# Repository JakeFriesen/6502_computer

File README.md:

2020-05-02
Jake Friesen
Using the VASM oldstyle assembler to convert assembly to a binary output for 6502 computers:

1) open CMD and cd to this folder, and have your assembly.txt in this folder
2) run the following command:
	vasm6502_oldstyle.exe -Fbin -dotdir YourFile.txt
-Fbin: outputs a binary file
-dotdir: uses the "." directives (like .org)
The binary file is the a.out file

3) open Xgpro, put the a.out file in, and configure for the right chip (ATMEL AT28C256)
4) load the chip into the programmer, and click "program"

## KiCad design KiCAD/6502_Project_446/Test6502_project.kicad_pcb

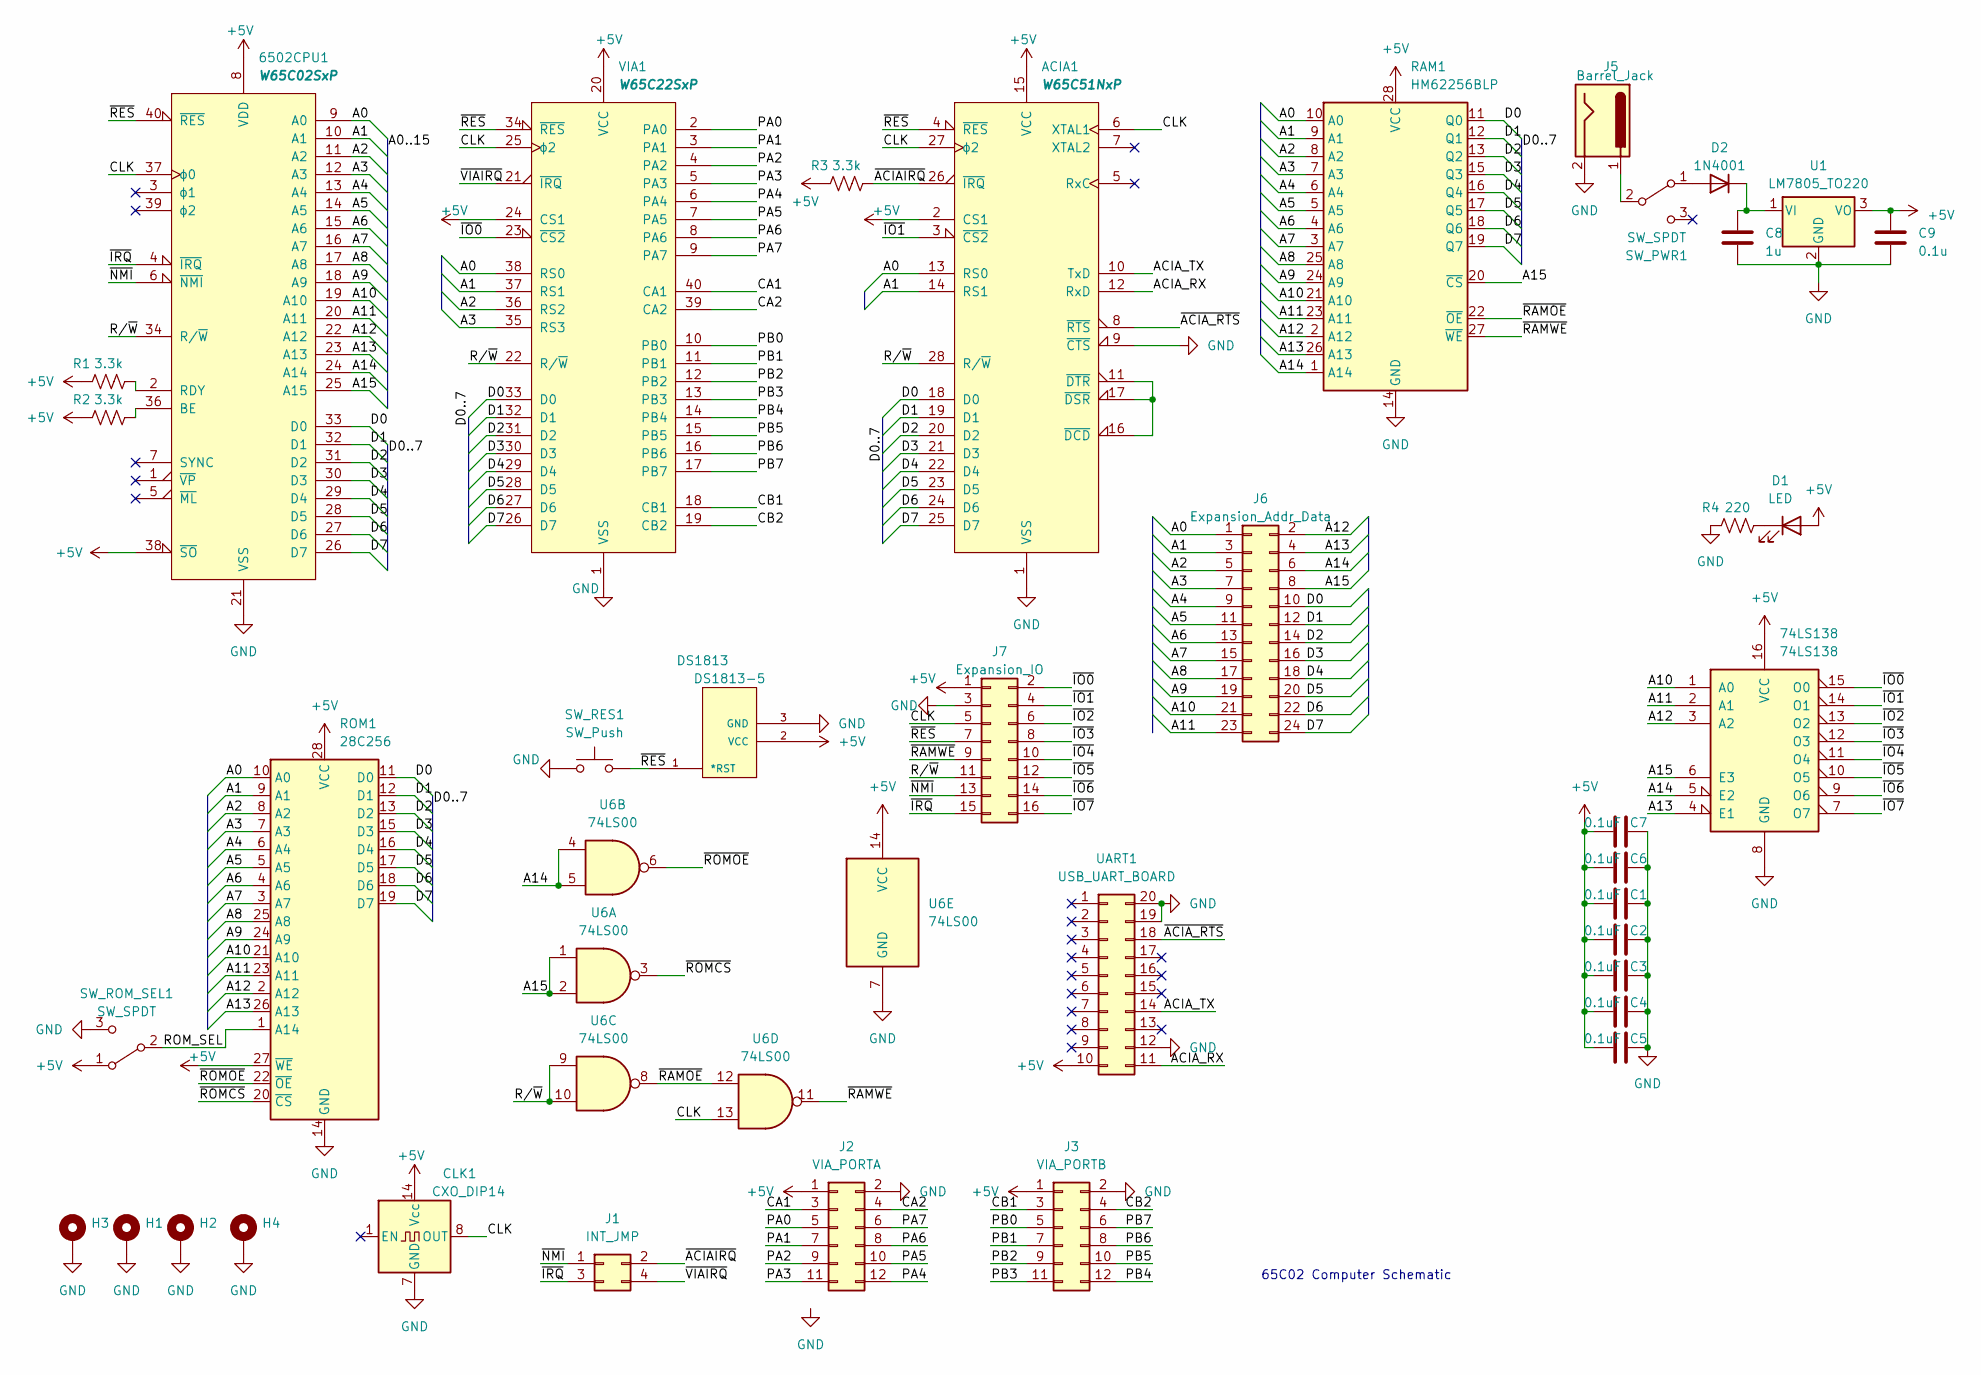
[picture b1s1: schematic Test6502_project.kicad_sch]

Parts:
74LS138: 74LS138; DIP-16_W7.62mm
6502CPU1: W65C02SxP; DIP-40_W15.24mm_Socket
ACIA1: W65C51NxP; DIP-28_W15.24mm_Socket
C1, C2, C3, C4, C5, C6, C7: 0.1uF; C_Disc_D5.0mm_W2.5mm_P2.50mm
C8: 1u; C_Disc_D5.0mm_W2.5mm_P2.50mm
C9: 0.1u; C_Disc_D5.0mm_W2.5mm_P2.50mm
CLK1: CXO_DIP14; Oscillator_DIP-14
D1: LED; LED_D3.0mm
D2: 1N4001; D_DO-41_SOD81_P10.16mm_Horizontal
DS1813: DS1813-5; 21-0248A; MANUFACTURER_PART_NUMBER ds18135+
H1, H2, H3, H4: MountingHole_Pad; MountingHole_3.2mm_M3_DIN965_Pad
J1: INT_JMP; PinHeader_2x02_P2.54mm_Vertical
J2: VIA_PORTA; PinHeader_2x06_P2.54mm_Vertical
J3: VIA_PORTB; PinHeader_2x06_P2.54mm_Vertical
J5: Barrel_Jack; BarrelJack_Horizontal
J6: Expansion_Addr_Data; PinHeader_2x12_P2.54mm_Vertical
J7: Expansion_IO; PinHeader_2x08_P2.54mm_Vertical
R1, R2, R3: 3.3k; R_Axial_DIN0207_L6.3mm_D2.5mm_P7.62mm_Horizontal
R4: 220; R_Axial_DIN0207_L6.3mm_D2.5mm_P7.62mm_Horizontal
RAM1: HM62256BLP; DIP-28_W15.24mm_Socket
ROM1: 28C256; DIP-28_W15.24mm_Socket
SW_PWR1: SW_SPDT; SW_THT_DPDT
SW_RES1: SW_Push; SW_PUSH_6mm
SW_ROM_SEL1: SW_SPDT; SW_THT_DPDT
U1: LM7805_TO220; TO-220-3_Vertical
U6: 74LS00; DIP-14_W7.62mm
UART1: USB_UART_BOARD; DIP-20_W15.24mm_UART
VIA1: W65C22SxP; DIP-40_W15.24mm_Socket

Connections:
+5V: 74LS138.16 (VCC), 6502CPU1.8 (VDD), 6502CPU1.38 (~SO), ACIA1.2 (CS1), ACIA1.15 (VCC), C1.1, C2.1, C3.1, C4.1, C5.1, C6.1, C7.1, C9.1, CLK1.14 (Vcc), D1.2 (A), DS1813.2 (VCC), J2.1, J3.1, J7.1, R1.1, R2.1, R3.1, RAM1.28 (VCC), ROM1.27 (~WE), ROM1.28 (VCC), SW_ROM_SEL1.1 (A), U1.3 (VO), U6.14 (VCC), UART1.10, VIA1.20 (VCC), VIA1.24 (CS1)
/A0: 6502CPU1.9 (A0), ACIA1.13 (RS0), J6.1, RAM1.10 (A0), ROM1.10 (A0), VIA1.38 (RS0)
/A1: 6502CPU1.10 (A1), ACIA1.14 (RS1), J6.3, RAM1.9 (A1), ROM1.9 (A1), VIA1.37 (RS1)
/A2: 6502CPU1.11 (A2), J6.5, RAM1.8 (A2), ROM1.8 (A2), VIA1.36 (RS2)
/A3: 6502CPU1.12 (A3), J6.7, RAM1.7 (A3), ROM1.7 (A3), VIA1.35 (RS3)
/A4: 6502CPU1.13 (A4), J6.9, RAM1.6 (A4), ROM1.6 (A4)
/A5: 6502CPU1.14 (A5), J6.11, RAM1.5 (A5), ROM1.5 (A5)
/A6: 6502CPU1.15 (A6), J6.13, RAM1.4 (A6), ROM1.4 (A6)
/A7: 6502CPU1.16 (A7), J6.15, RAM1.3 (A7), ROM1.3 (A7)
/A8: 6502CPU1.17 (A8), J6.17, RAM1.25 (A8), ROM1.25 (A8)
/A9: 6502CPU1.18 (A9), J6.19, RAM1.24 (A9), ROM1.24 (A9)
/A10: 74LS138.1 (A0), 6502CPU1.19 (A10), J6.21, RAM1.21 (A10), ROM1.21 (A10)
/A11: 74LS138.2 (A1), 6502CPU1.20 (A11), J6.23, RAM1.23 (A11), ROM1.23 (A11)
/A12: 74LS138.3 (A2), 6502CPU1.22 (A12), J6.2, RAM1.2 (A12), ROM1.2 (A12)
/A13: 74LS138.4 (E1), 6502CPU1.23 (A13), J6.4, RAM1.26 (A13), ROM1.26 (A13)
/A14: 74LS138.5 (E2), 6502CPU1.24 (A14), J6.6, RAM1.1 (A14), U6.4, U6.5
/A15: 74LS138.6 (E3), 6502CPU1.25 (A15), J6.8, RAM1.20 (~CS), U6.1, U6.2
/ACIA_RX: ACIA1.12 (RxD), UART1.11
/ACIA_TX: ACIA1.10 (TxD), UART1.14
/CA1: J2.3, VIA1.40 (CA1)
/CA2: J2.4, VIA1.39 (CA2)
/CB1: J3.3, VIA1.18 (CB1)
/CB2: J3.4, VIA1.19 (CB2)
/CLK: 6502CPU1.37 (ϕ0), ACIA1.6 (XTAL1), ACIA1.27 (ϕ2), CLK1.8 (OUT), J7.5, U6.13, VIA1.25 (ϕ2)
/D0: 6502CPU1.33 (D0), ACIA1.18 (D0), J6.10, RAM1.11 (Q0), ROM1.11 (D0), VIA1.33 (D0)
/D1: 6502CPU1.32 (D1), ACIA1.19 (D1), J6.12, RAM1.12 (Q1), ROM1.12 (D1), VIA1.32 (D1)
/D2: 6502CPU1.31 (D2), ACIA1.20 (D2), J6.14, RAM1.13 (Q2), ROM1.13 (D2), VIA1.31 (D2)
/D3: 6502CPU1.30 (D3), ACIA1.21 (D3), J6.16, RAM1.15 (Q3), ROM1.15 (D3), VIA1.30 (D3)
/D4: 6502CPU1.29 (D4), ACIA1.22 (D4), J6.18, RAM1.16 (Q4), ROM1.16 (D4), VIA1.29 (D4)
/D5: 6502CPU1.28 (D5), ACIA1.23 (D5), J6.20, RAM1.17 (Q5), ROM1.17 (D5), VIA1.28 (D5)
/D6: 6502CPU1.27 (D6), ACIA1.24 (D6), J6.22, RAM1.18 (Q6), ROM1.18 (D6), VIA1.27 (D6)
/D7: 6502CPU1.26 (D7), ACIA1.25 (D7), J6.24, RAM1.19 (Q7), ROM1.19 (D7), VIA1.26 (D7)
/PA0: J2.5, VIA1.2 (PA0)
/PA1: J2.7, VIA1.3 (PA1)
/PA2: J2.9, VIA1.4 (PA2)
/PA3: J2.11, VIA1.5 (PA3)
/PA4: J2.12, VIA1.6 (PA4)
/PA5: J2.10, VIA1.7 (PA5)
/PA6: J2.8, VIA1.8 (PA6)
/PA7: J2.6, VIA1.9 (PA7)
/PB0: J3.5, VIA1.10 (PB0)
/PB1: J3.7, VIA1.11 (PB1)
/PB2: J3.9, VIA1.12 (PB2)
/PB3: J3.11, VIA1.13 (PB3)
/PB4: J3.12, VIA1.14 (PB4)
/PB5: J3.10, VIA1.15 (PB5)
/PB6: J3.8, VIA1.16 (PB6)
/PB7: J3.6, VIA1.17 (PB7)
/ROM_SEL: ROM1.1 (A14), SW_ROM_SEL1.2 (B)
/R/~W: 6502CPU1.34 (R/~W), ACIA1.28 (R/~W), J7.11, U6.9, U6.10, VIA1.22 (R/~W)
/~ACIAIRQ: ACIA1.26 (~IRQ), J1.2, R3.2
/~ACIA_RTS: ACIA1.8 (~RTS), UART1.18
/~IO0: 74LS138.15 (O0), J7.2, VIA1.23 (~CS2)
/~IO1: 74LS138.14 (O1), ACIA1.3 (~CS2), J7.4
/~IO2: 74LS138.13 (O2), J7.6
/~IO3: 74LS138.12 (O3), J7.8
/~IO4: 74LS138.11 (O4), J7.10
/~IO5: 74LS138.10 (O5), J7.12
/~IO6: 74LS138.9 (O6), J7.14
/~IO7: 74LS138.7 (O7), J7.16
/~IRQ: 6502CPU1.4 (~IRQ), J1.3, J7.15
/~NMI: 6502CPU1.6 (~NMI), J1.1, J7.13
/~RAMOE: RAM1.22 (~OE), U6.8, U6.12
/~RAMWE: J7.9, RAM1.27 (~WE), U6.11
/~RES: 6502CPU1.40 (~RES), ACIA1.4 (~RES), DS1813.1 (*RST), J7.7, SW_RES1.2, VIA1.34 (~RES)
/~ROMCS: ROM1.20 (~CS), U6.3
/~ROMOE: ROM1.22 (~OE), U6.6
/~VIAIRQ: J1.4, VIA1.21 (~IRQ)
GND: 74LS138.8 (GND), 6502CPU1.21 (VSS), ACIA1.1 (VSS), ACIA1.9 (~CTS), C1.2, C2.2, C3.2, C4.2, C5.2, C6.2, C7.2, C8.2, C9.2, CLK1.7 (GND), DS1813.3 (GND), H1.1, H2.1, H3.1, H4.1, J2.2, J3.2, J5.2, J7.3, R4.1, RAM1.14 (GND), ROM1.14 (GND), SW_RES1.1, SW_ROM_SEL1.3 (C), U1.2 (GND), U6.7 (GND), UART1.12, UART1.19, UART1.20, VIA1.1 (VSS)
unnamed: 6502CPU1.36 (BE), R2.2
unnamed: 6502CPU1.2 (RDY), R1.2
unnamed: ACIA1.11 (~DTR), ACIA1.16 (~DCD), ACIA1.17 (~DSR)
unnamed: D1.1 (K), R4.2
unnamed: D2.2 (A), SW_PWR1.1 (A)
unnamed: C8.1, D2.1 (K), U1.1 (VI)
unnamed: J5.1, SW_PWR1.2 (B)

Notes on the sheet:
65C02 Computer Schematic

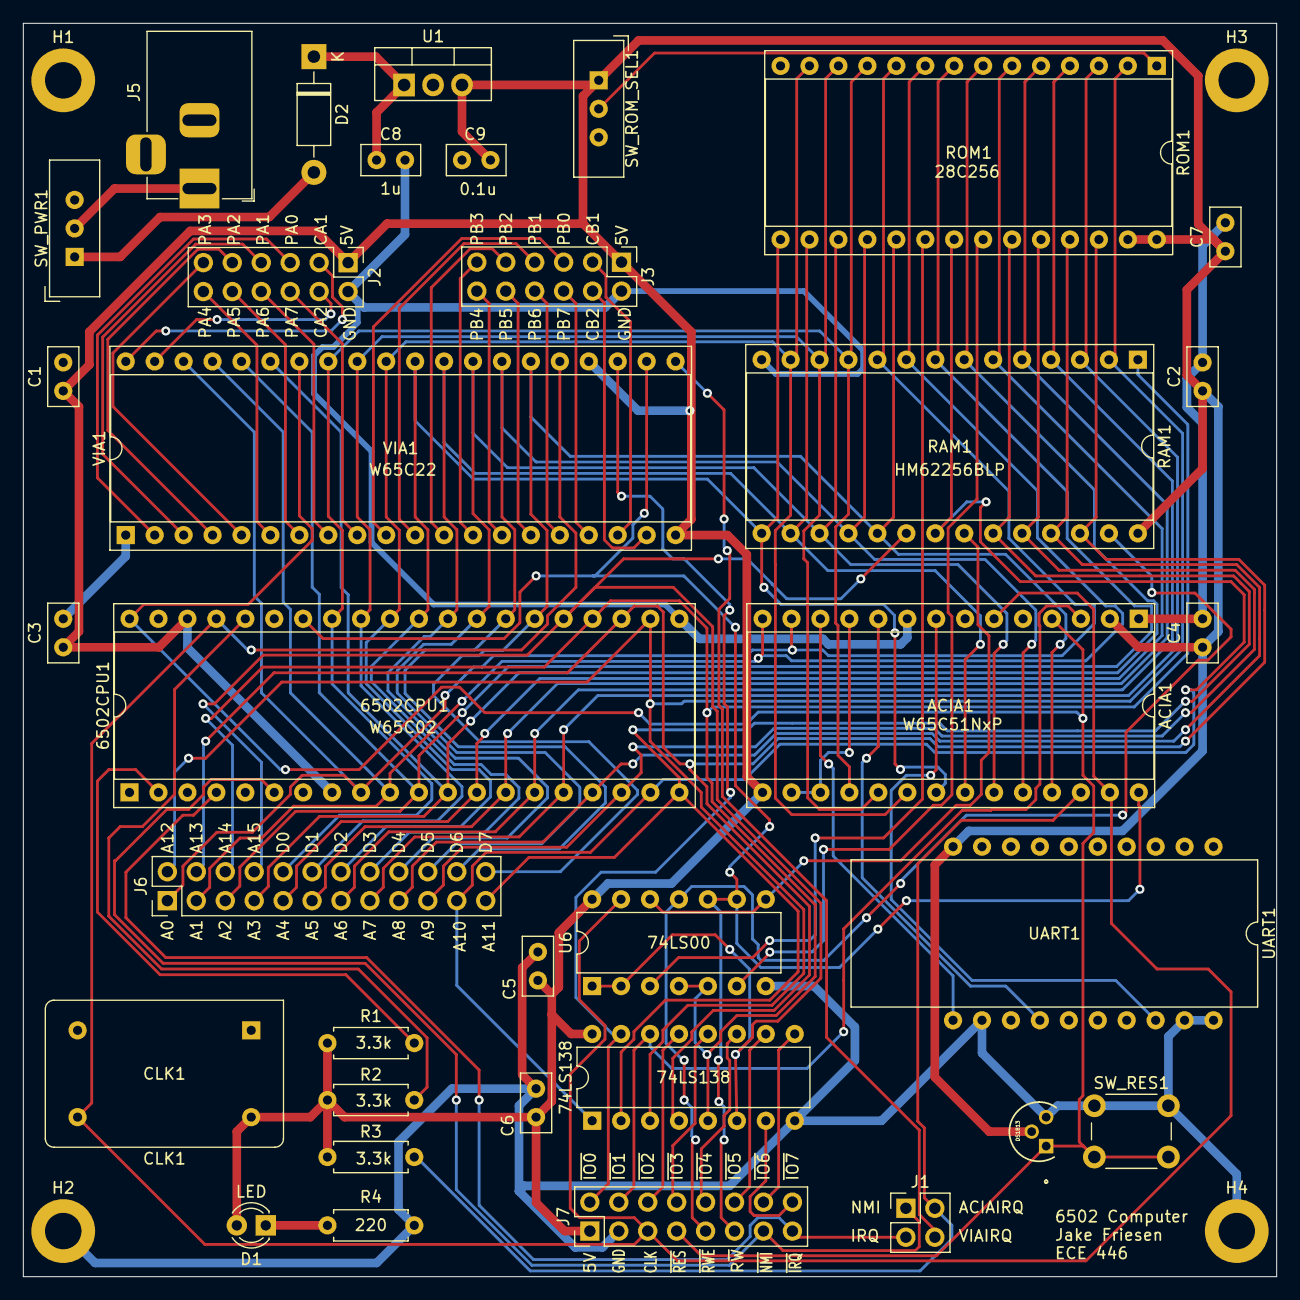
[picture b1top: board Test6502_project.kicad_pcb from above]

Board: 2 copper layers, 110.0 x 110.0 mm, 39 parts (0 on the bottom side), 76 nets.

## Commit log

2021-10-15 repo created
2021-10-17 Serial transfer works
2021-10-18 Code separated into libraries
2021-10-18 Serial receive working
2021-10-25 Unmodified xmodem library
2021-12-13 adding so I don't lose files
2022-09-07 new mem map
2022-09-08 Conversion to cc65 successful! Still very rough
2022-09-09 Makefile to run assembler and linker
2023-07-18 Added KiCAD project
